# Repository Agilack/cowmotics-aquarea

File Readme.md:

Cowmotics Aquarea
=================

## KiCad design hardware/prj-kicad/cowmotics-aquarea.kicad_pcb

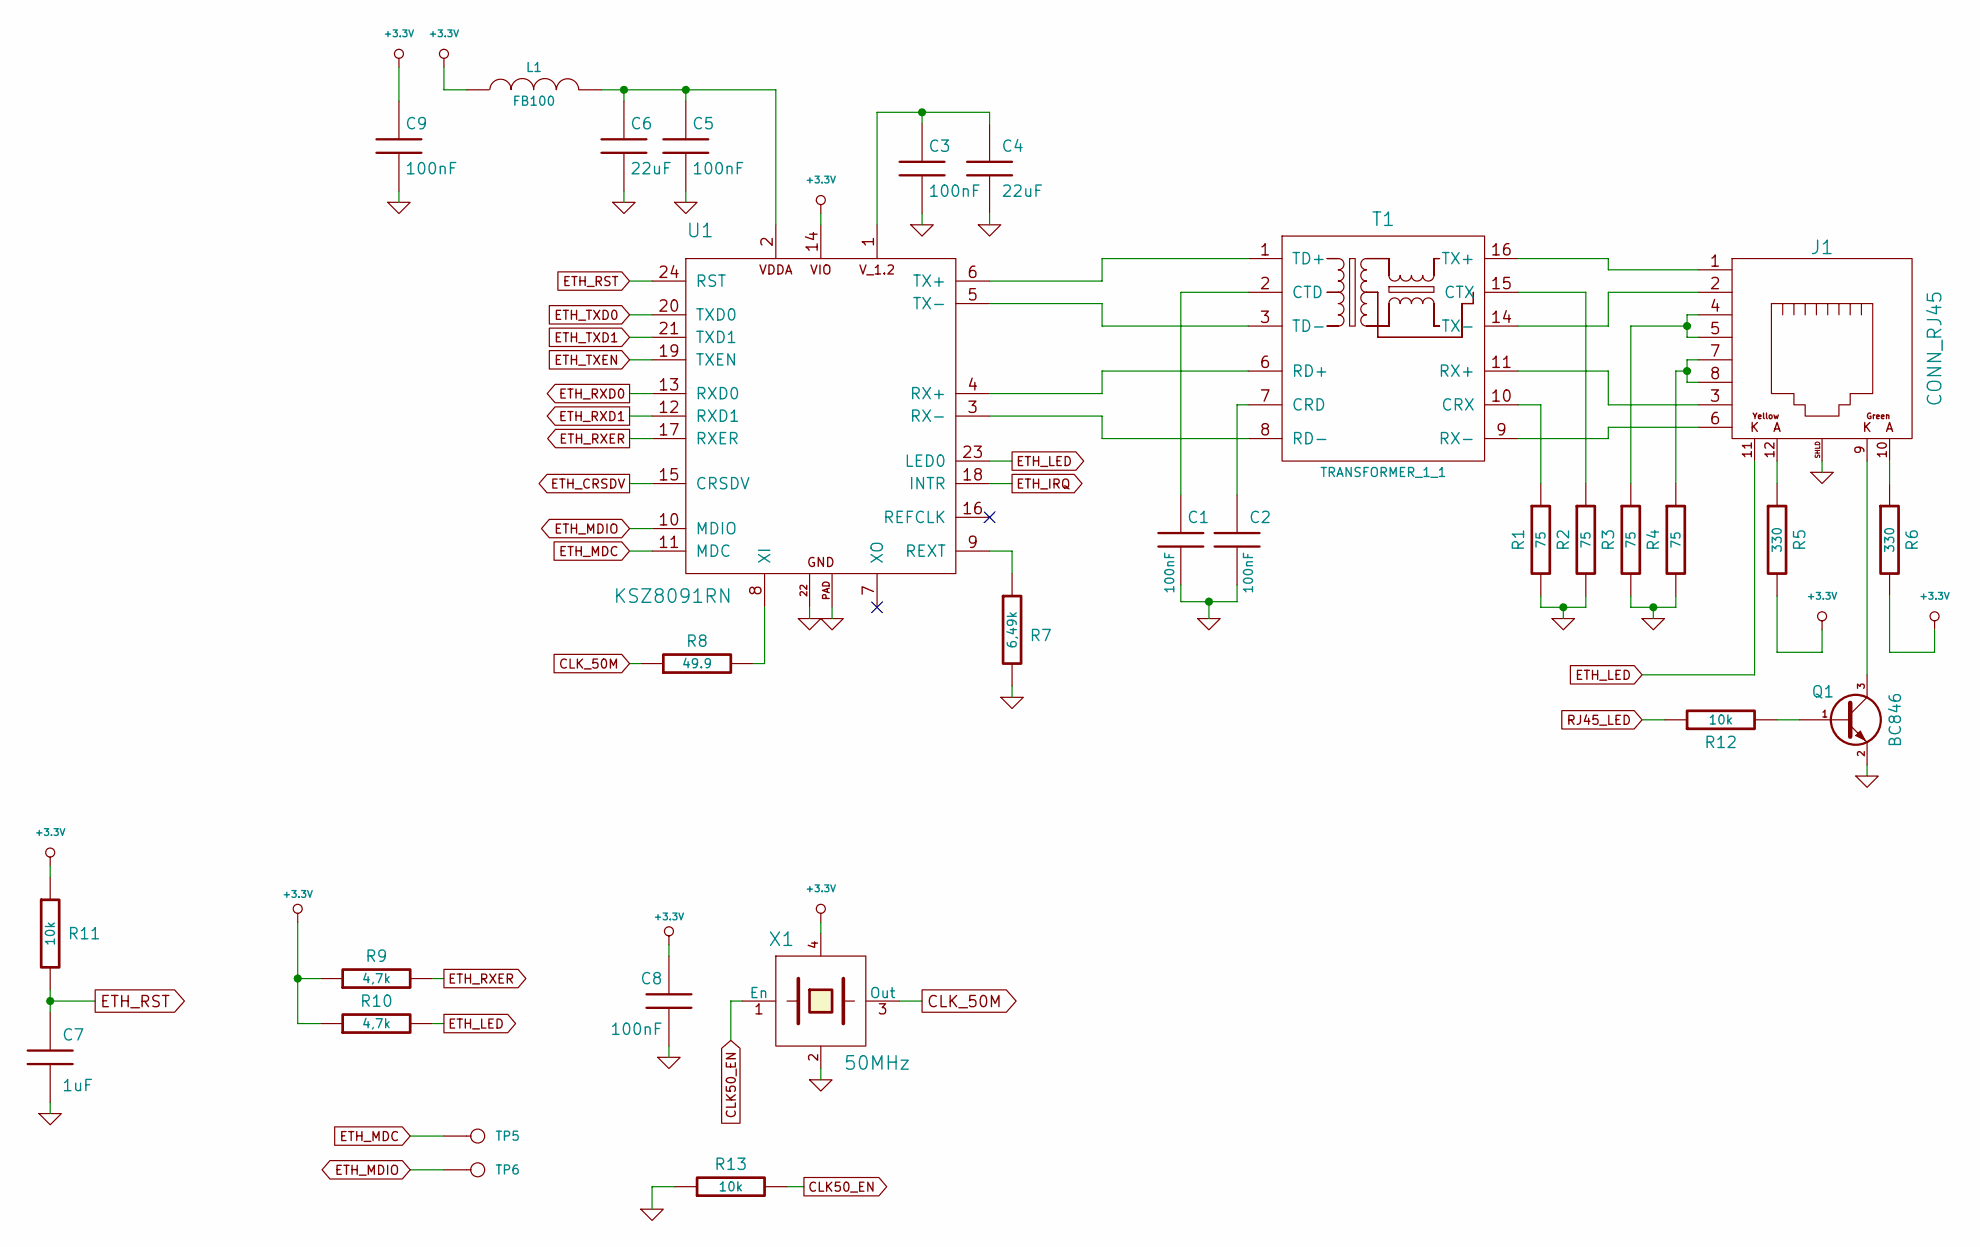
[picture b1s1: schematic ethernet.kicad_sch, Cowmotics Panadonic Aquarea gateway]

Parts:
C1, C2, C3, C5, C8, C9: 100nF; SMD0603
C4, C6: 22uF; SMD0805
C7: 1uF; SMD0603
J1: CONN_RJ45; CONN_615008185121
L1: FB100; SMD0603
Q1: BC846; SOT23-3
R1, R2, R3, R4: 75; SMD0603
R5, R6: 330; SMD0603
R7: 6,49k; SMD0603
R8: 49.9; SMD0603
R9, R10: 4,7k; SMD0603
R11, R12, R13: 10k; SMD0603
T1: TRANSFORMER_1_1; TR_W749013011
TP5, TP6: CONN_1; TP_SMD
U1: KSZ8091RN; QFN24
X1: 50MHz; Q_SMD5x3

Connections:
+3.3V: C8.1, C9.1, L1.1, R5.2, R6.2, R9.1, R10.1, R11.1, U1.14, X1.4; also elsewhere on the board
CLK50_EN: R13.2, X1.1 (En); also elsewhere on the board
CLK_50M: R8.1, X1.3 (Out); also elsewhere on the board
ETH_CRSDV: U1.15 (CRSDV); also elsewhere on the board
ETH_IRQ: U1.18 (INTR); also elsewhere on the board
ETH_LED: J1.11, R10.2, U1.23 (LED0)
ETH_MDC: TP5.1, U1.11 (MDC); also elsewhere on the board
ETH_MDIO: TP6.1, U1.10 (MDIO); also elsewhere on the board
ETH_RST: C7.1, R11.2, U1.24 (RST)
ETH_RXD0: U1.13 (RXD0); also elsewhere on the board
ETH_RXD1: U1.12 (RXD1); also elsewhere on the board
ETH_RXER: R9.2, U1.17 (RXER); also elsewhere on the board
ETH_TXD0: U1.20 (TXD0); also elsewhere on the board
ETH_TXD1: U1.21 (TXD1); also elsewhere on the board
ETH_TXEN: U1.19 (TXEN); also elsewhere on the board
GND: C1.2, C2.2, C3.2, C4.2, C5.2, C6.2, C7.2, C8.2, C9.2, J1.SHLD, Q1.2 (E), R1.2, R2.2, R3.2, R4.2, R7.2, R13.1, U1.22, U1.PAD, X1.2; also elsewhere on the board
unnamed: C1.1, T1.2 (CTD)
unnamed: C2.1, T1.7 (CRD)
unnamed: C3.1, C4.1, U1.1
unnamed: C5.1, C6.1, L1.2, U1.2
unnamed: J1.1, T1.16 (TX+)
unnamed: J1.2, T1.14 (TX-)
unnamed: J1.3, T1.11 (RX+)
unnamed: J1.4, J1.5, R3.1
unnamed: J1.6, T1.9 (RX-)
unnamed: J1.7, J1.8, R4.1
unnamed: J1.9, Q1.3 (C)
unnamed: J1.10, R6.1
unnamed: J1.12, R5.1
unnamed: Q1.1 (B), R12.2
unnamed: R1.1, T1.10 (CRX)
unnamed: R2.1, T1.15 (CTX)
unnamed: R7.1, U1.9 (REXT)
unnamed: R8.2, U1.8 (XI)
unnamed: T1.1 (TD+), U1.6 (TX+)
unnamed: T1.3 (TD-), U1.5 (TX-)
unnamed: T1.6 (RD+), U1.4 (RX+)
unnamed: T1.8 (RD-), U1.3 (RX-)
RJ45_LED: R12.1; also elsewhere on the board

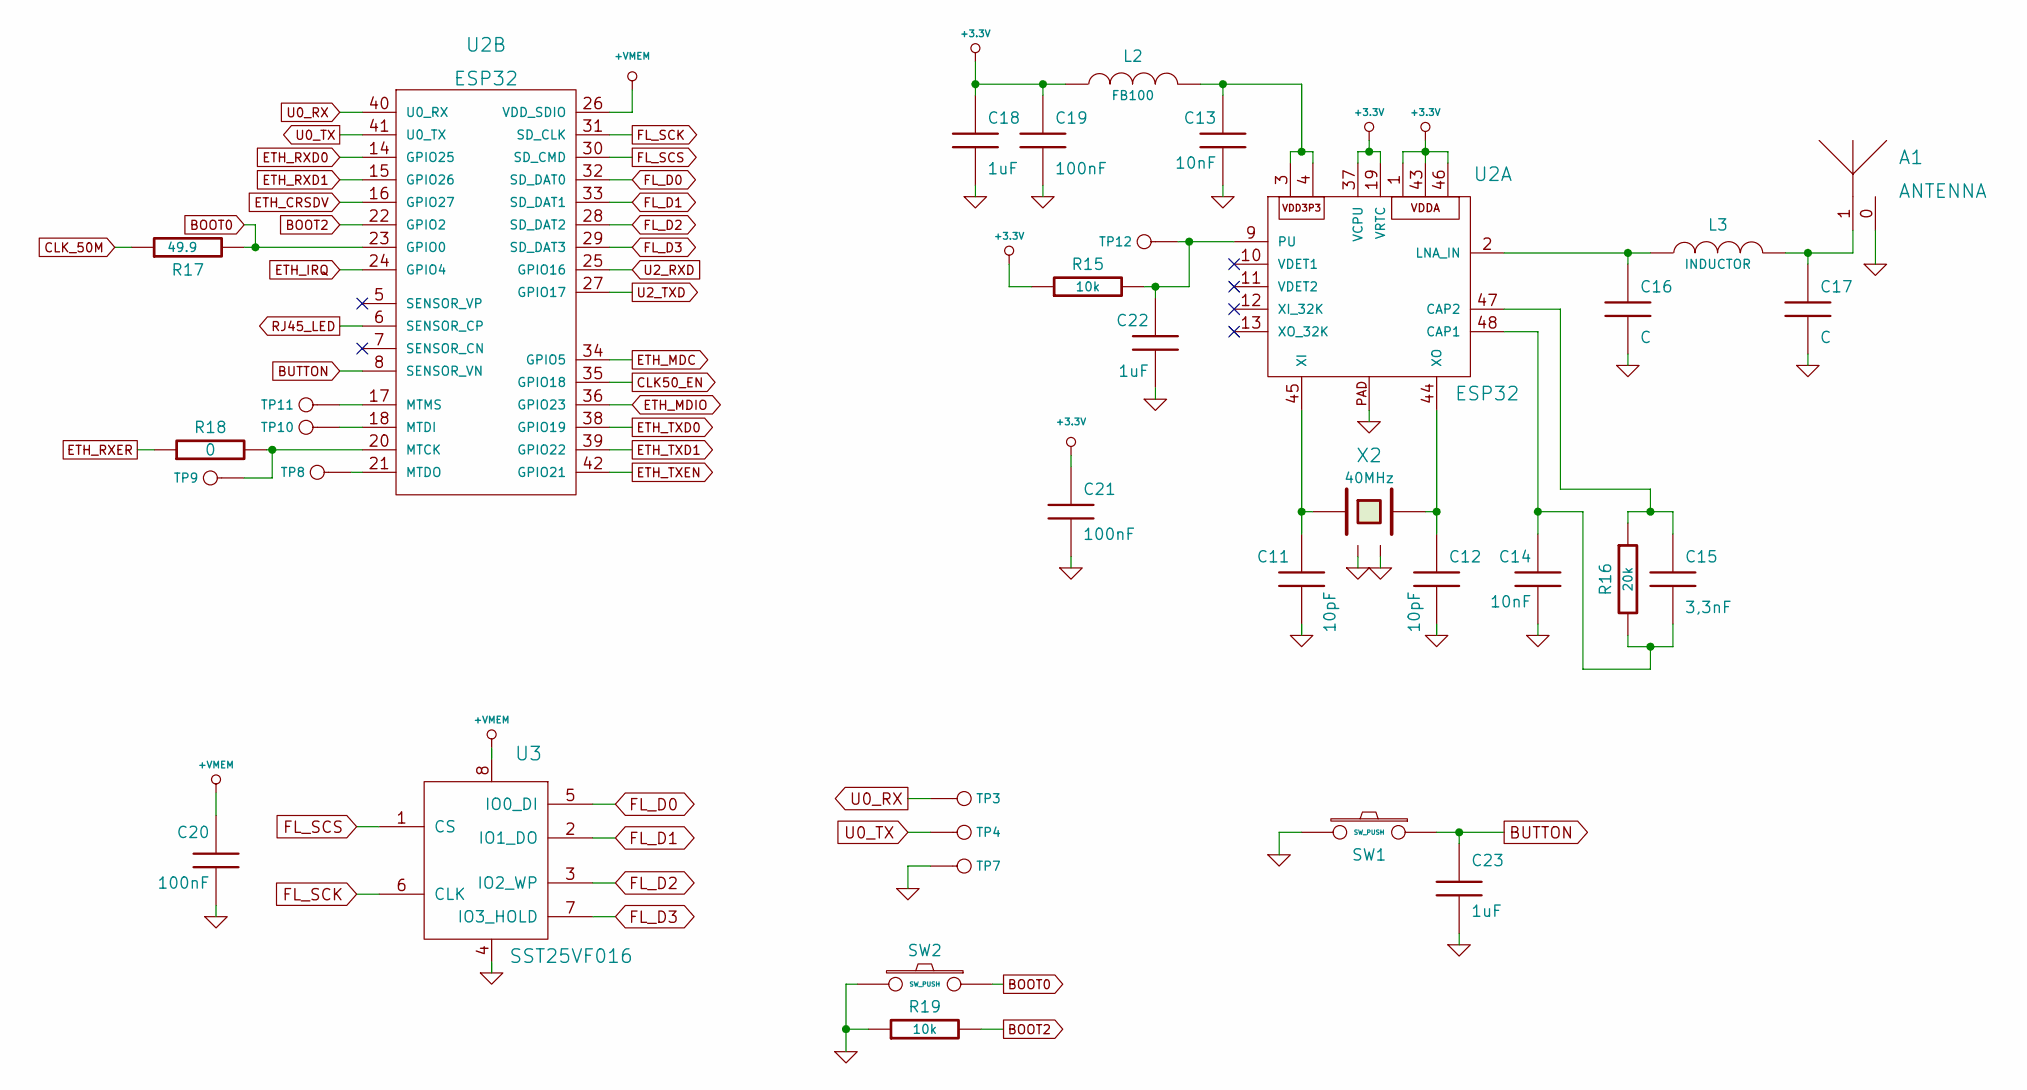
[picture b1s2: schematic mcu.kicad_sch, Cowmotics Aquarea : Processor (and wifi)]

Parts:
A1: ANTENNA; CONN_SMA_RA
C11, C12: 10pF; SMD0603
C13, C14: 10nF; SMD0603
C15: 3,3nF; SMD0603
C16, C17: C; SMD0603
C18, C22, C23: 1uF; SMD0603
C19, C20, C21: 100nF; SMD0603
L2: FB100; SMD0603
L3: INDUCTOR; SMD0603
R15, R19: 10k; SMD0603
R16: 20k; SMD0603
R17: 49.9; SMD0603
R18: 0; SMD0603
SW1: SW_PUSH; SW_PTS840
SW2: SW_PUSH; SW_434123043816
TP3, TP4, TP7, TP8, TP9, TP10, TP11, TP12: CONN_1; TP_SMD
U2: ESP32; QFN48-04
U3: SST25VF016; SOIC-8
X2: 40MHz; Q_3.2x2.5

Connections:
+3.3V: C18.1, C19.1, C21.1, L2.1, R15.1, U2.1, U2.19 (VRTC), U2.37 (VCPU), U2.43, U2.46; also elsewhere on the board
+VMEM: C20.1, U2.26 (VDD_SDIO), U3.8
BOOT0: R17.2, SW2.1, U2.23 (GPIO0)
BOOT2: R19.2, U2.22 (GPIO2)
BUTTON: C23.1, SW1.1, U2.8 (SENSOR_VN)
CLK50_EN: U2.35 (GPIO18); also elsewhere on the board
CLK_50M: R17.1; also elsewhere on the board
ETH_CRSDV: U2.16 (GPIO27); also elsewhere on the board
ETH_IRQ: U2.24 (GPIO4); also elsewhere on the board
ETH_MDC: U2.34 (GPIO5); also elsewhere on the board
ETH_MDIO: U2.36 (GPIO23); also elsewhere on the board
ETH_RXD0: U2.14 (GPIO25); also elsewhere on the board
ETH_RXD1: U2.15 (GPIO26); also elsewhere on the board
ETH_RXER: R18.1; also elsewhere on the board
ETH_TXD0: U2.38 (GPIO19); also elsewhere on the board
ETH_TXD1: U2.39 (GPIO22); also elsewhere on the board
ETH_TXEN: U2.42 (GPIO21); also elsewhere on the board
FL_D0: U2.32 (SD_DAT0), U3.5 (IO0_DI)
FL_D1: U2.33 (SD_DAT1), U3.2 (IO1_DO)
FL_D2: U2.28 (SD_DAT2), U3.3 (IO2_WP)
FL_D3: U2.29 (SD_DAT3), U3.7 (IO3_HOLD)
FL_SCK: U2.31 (SD_CLK), U3.6 (CLK)
FL_SCS: U2.30 (SD_CMD), U3.1 (CS)
GND: A1.0, C11.2, C12.2, C13.2, C14.2, C16.2, C17.2, C18.2, C19.2, C20.2, C21.2, C22.2, C23.2, R19.1, SW1.2, SW2.2, TP7.1, U2.PAD, U3.4, X2.2, X2.4; also elsewhere on the board
unnamed: A1.1, C17.1, L3.2
unnamed: C11.1, U2.45 (XI), X2.3
unnamed: C12.1, U2.44 (XO), X2.1
unnamed: C13.1, L2.2, U2.3, U2.4
unnamed: C14.1, C15.2, R16.2, U2.48 (CAP1)
unnamed: C15.1, R16.1, U2.47 (CAP2)
unnamed: C16.1, L3.1, U2.2 (LNA_IN)
unnamed: C22.1, R15.2, TP12.1, U2.9 (PU)
unnamed: R18.2, TP9.1, U2.20 (MTCK)
unnamed: TP8.1, U2.21 (MTDO)
unnamed: TP10.1, U2.18 (MTDI)
unnamed: TP11.1, U2.17 (MTMS)
RJ45_LED: U2.6 (SENSOR_CP); also elsewhere on the board
U0_RX: TP3.1, U2.40 (U0_RX)
U0_TX: TP4.1, U2.41 (U0_TX)
U2_RXD: U2.25 (GPIO16); also elsewhere on the board
U2_TXD: U2.27 (GPIO17); also elsewhere on the board

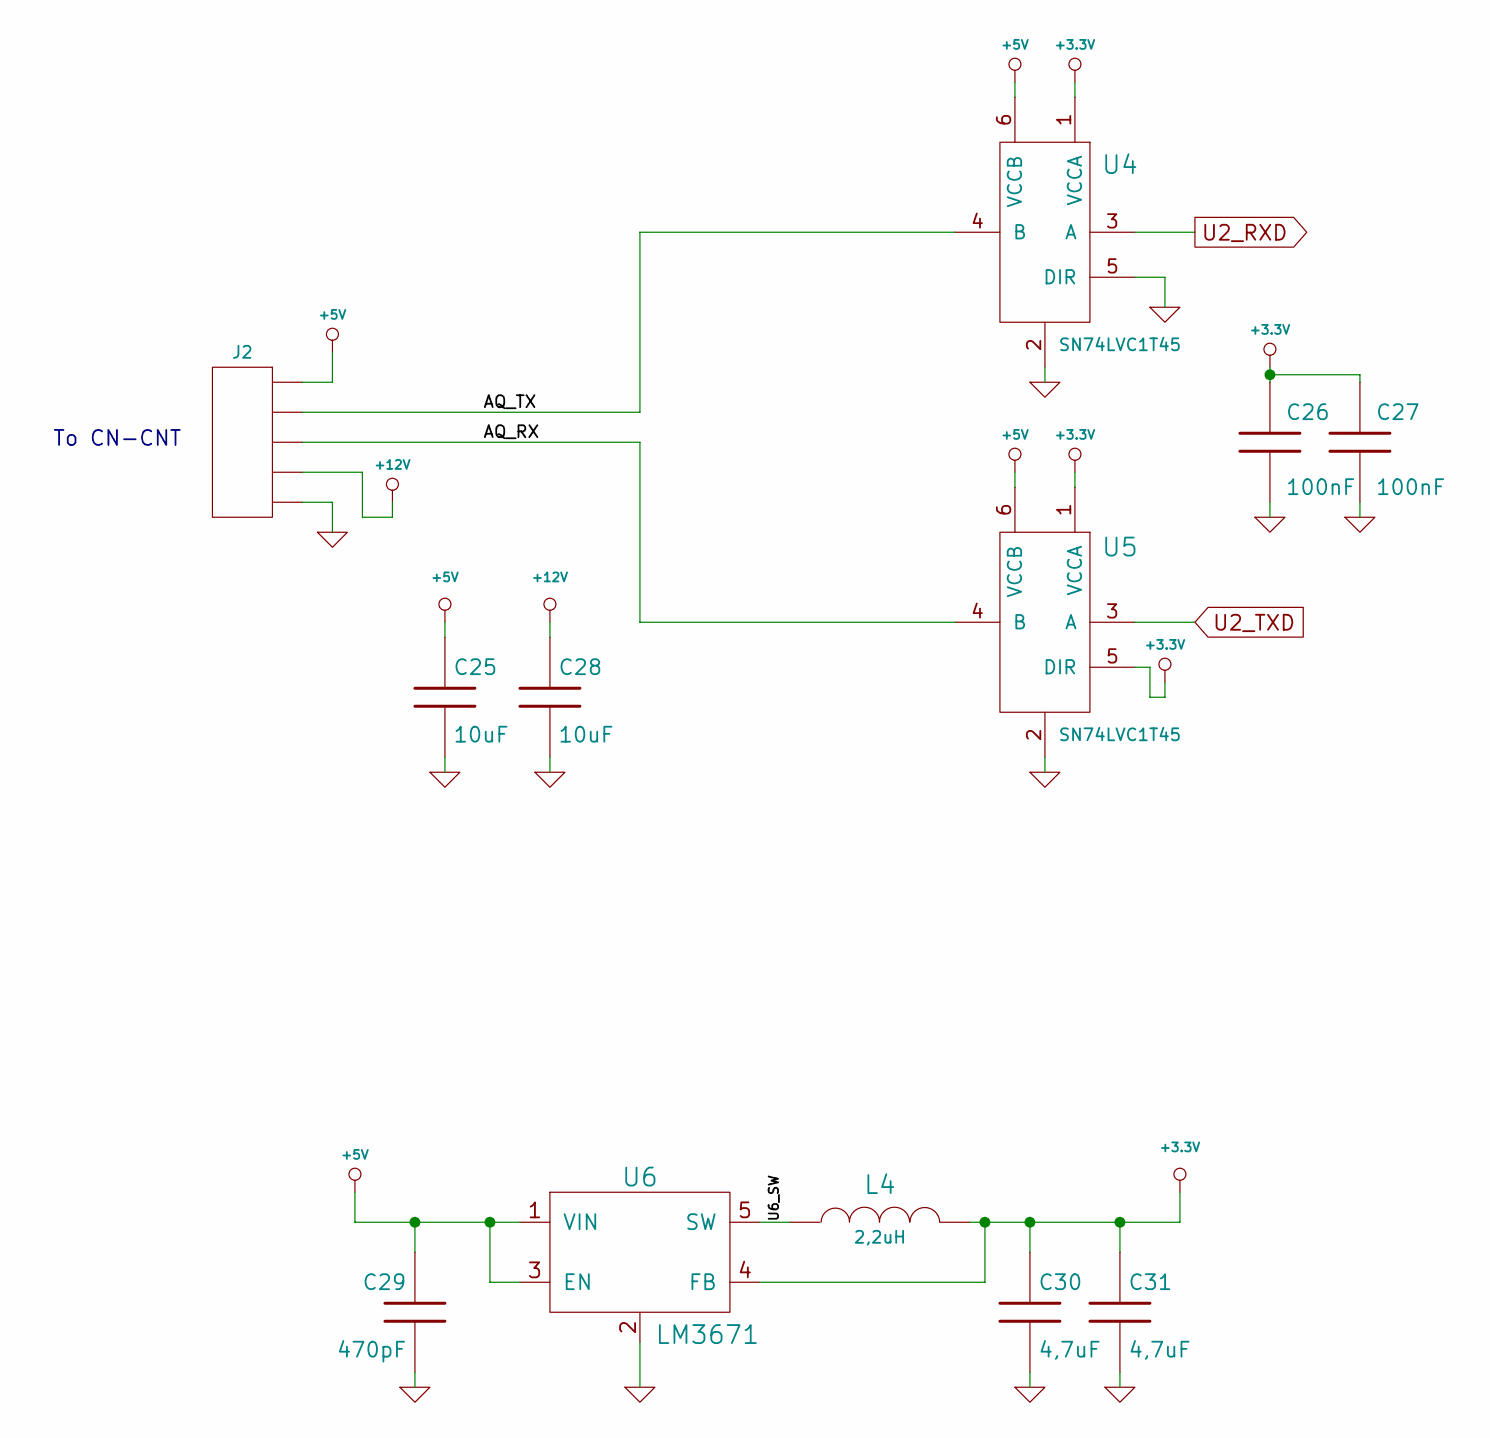
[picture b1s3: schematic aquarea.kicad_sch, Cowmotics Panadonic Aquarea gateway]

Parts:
C25, C28: 10uF; SMD1210
C26, C27: 100nF; SMD0603
C29: 470pF; SMD0603
C30, C31: 4,7uF; SMD0603
J2: CONN_5; CONN_691243310005
L4: 2,2uH; I_CDRH2D14
U4, U5: SN74LVC1T45; SOT23-6
U6: LM3671; SOT23-5

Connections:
+3.3V: C26.1, C27.1, C30.1, C31.1, L4.2, U4.1 (VCCA), U5.1 (VCCA), U5.5 (DIR), U6.4 (FB); also elsewhere on the board
+5V: C25.1, C29.1, J2.1, U4.6 (VCCB), U5.6 (VCCB), U6.1 (VIN), U6.3 (EN)
+12V: C28.1, J2.4
/Aquarea Interface/AQ_RX: J2.3, U5.4 (B)
/Aquarea Interface/AQ_TX: J2.2, U4.4 (B)
/Aquarea Interface/U6_SW: L4.1, U6.5 (SW)
GND: C25.2, C26.2, C27.2, C28.2, C29.2, C30.2, C31.2, J2.5, U4.2, U4.5 (DIR), U5.2, U6.2; also elsewhere on the board
U2_RXD: U4.3 (A); also elsewhere on the board
U2_TXD: U5.3 (A); also elsewhere on the board

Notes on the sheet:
To CN-CNT

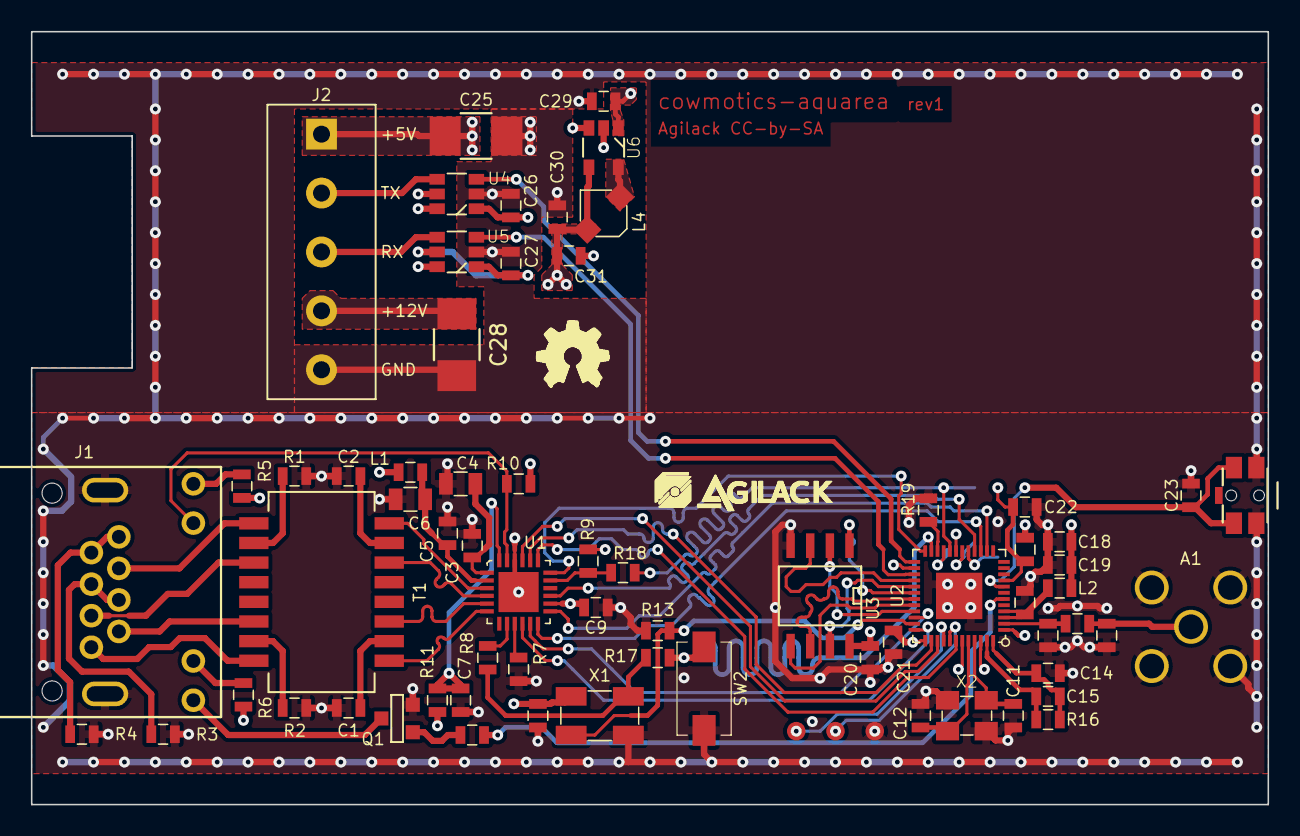
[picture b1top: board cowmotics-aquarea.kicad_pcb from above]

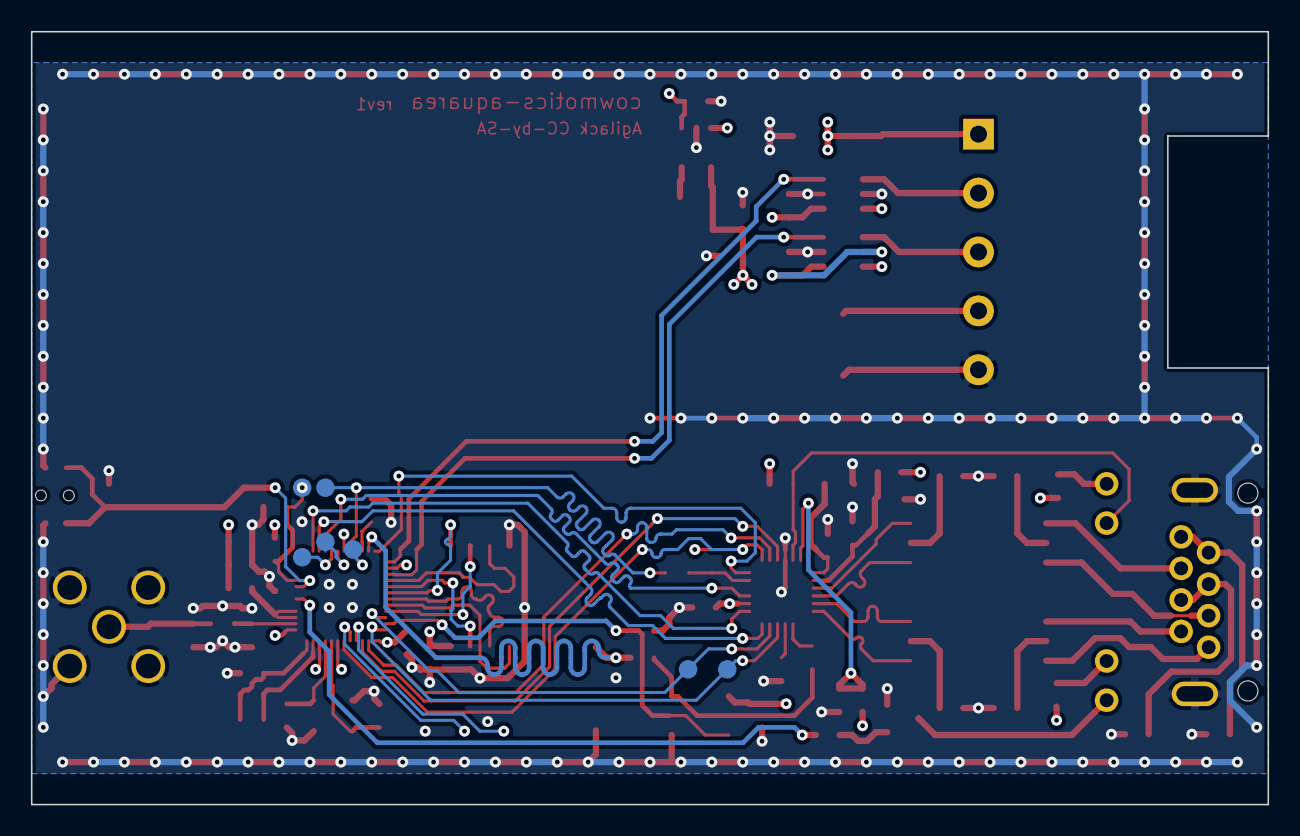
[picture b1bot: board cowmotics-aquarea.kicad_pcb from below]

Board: 4 copper layers, 80.0 x 50.0 mm, 78 parts (7 on the bottom side), 70 nets.

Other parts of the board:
agilack-11.5: 450px; logo-agilack-11.5
ohw_logo: VAL**; logo-ohw

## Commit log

2022-01-10 = Create project, add board skeleton, insert ethernet (sch+routing)
2022-01-11 = ADD: Insert ESP32 processor and his main components
2022-01-12 = UPD: Finish ESP32 routing (eth, boot, console, ...)
2022-01-13 = ADD: Insert Aquarea serial interface and power supply
2022-01-14 = ADD: Create production files for rev1
2022-01-16 Firmware: Create basic/skeleton firmware to read Aquarea status
2022-01-22 Firmware: Insert a module for low-level aquarea communiation (uart reception)
2022-01-23 Firmware: Improve low-level uart and create a functional module for Aquarea

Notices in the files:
hardware/prj-kicad/aquarea.kicad_sch:
Licence: CC-by-SA
hardware/prj-kicad/cowmotics-aquarea.kicad_pcb:
Agilack CC-by-SA
